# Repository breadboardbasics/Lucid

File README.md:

This is a repository for my Hackaday project here: http://hackaday.io/project/3715-tacs-lucid-dreaming-device

Thanks for checking out my project!
To make everything easier just click the download zip button on the right side of the main page of this repository. 
Then extract everthing to a folder. Next you should be able to view the board and schematic files with KiCad or
you can just view the schematic with the pdf that I included. 

All code that is used in this project will also be posted in this repository and will be updated as I progress through the 
project. 

Also for those wondering RevA (Revision A) is what I am calling the first version of the hardware. It is still a work in 
progress but is almost complete and ready for testing. 

**Disclaimer** - I am not responsible for any damages or injury related to this project
The project is very safe. It is battery powered and has a maximum of about 18v present on the board. Do not attempt to use 
the headset when it is connected to mains (the wall) in any way ex. you are powereing it with the programmer which is connected 
a desktop computer ect.

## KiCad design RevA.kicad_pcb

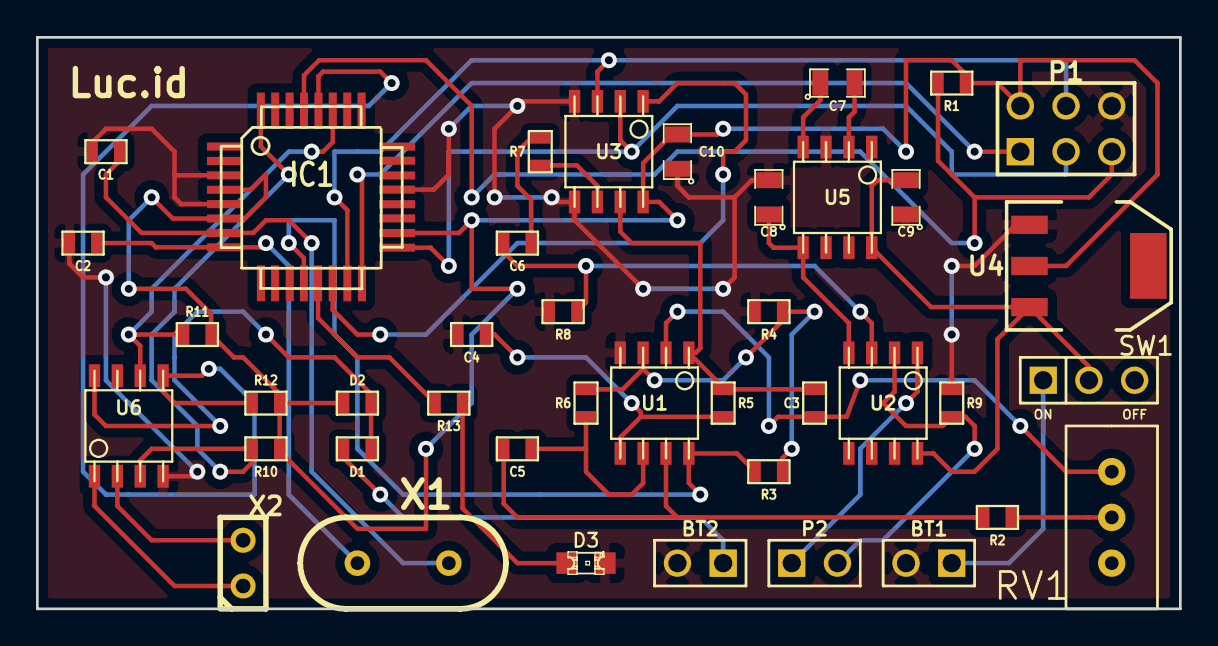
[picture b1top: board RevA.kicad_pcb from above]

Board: 2 copper layers, 63.5 x 31.8 mm, 41 parts (0 on the bottom side), 36 nets.

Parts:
BT1, BT2: BATTERY; PIN_ARRAY_2X1
C1, C2: 22pF; SM0603
C3, C4, C5, C6: .22uF; SM0603
C7, C8, C9, C10: 10uF; SM0805
D1, D2: DIODE; SM0603
D3: LED; LED-0805
IC1: ATMEGA328P-A; TQFP32
P1: ICSP; pin_array_3x2
P2: ELECTODES; PIN_ARRAY_2X1
R1, R2, R7, R10, R11, R12: 10k; SM0603
R3, R4: 2.2k; SM0603
R5, R6: 13k; SM0603
R8: 10M; SM0603
R9: 2.5k; SM0603
R13: 3.3k; SM0603
RV1: 20k; TRIMPOT_V
SW1: Power Switch; PIN_ARRAY_3X1
U1, U2: LM358; so-8
U3: MCP41010; so-8
U4: LM1117; SOT223
U5: ICL7660; so-8
U6: PCF8563; so-8
X1: 16MHz; HC-49V
X2: 32.768kHz; C1

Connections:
+5V: C10.2, D2.1, IC1.4, IC1.6, IC1.18, P1.2, R1.2, R10.2, R11.2, R12.2, U3.8, U4.2
+9V: C9.2, SW1.2, U2.8, U4.3, U5.8
-8V: C8.1, U2.4, U5.5
/INT: IC1.32, R10.1, U6.3
/MISO: IC1.16, P1.1
/MOSI: IC1.15, P1.4, U3.3
/OCON: IC1.12, R3.1, U1.8
/RST: IC1.29, P1.5, R1.1
/RTC_SCL: IC1.28, R12.1, U6.5
/RTC_SDA: IC1.27, R11.1, U6.6
/SCK: IC1.17, P1.3, U3.2
/led: IC1.13, R13.1
/potB: C3.2, R5.2, U1.1, U3.7
/potCS: IC1.14, U3.1
/potWiper: R7.1, U3.6
GND: BT1.2, BT2.2, C1.2, C2.2, C4.1, C8.2, C9.1, C10.1, D3.2, IC1.3, IC1.5, IC1.21, P1.6, R4.2, R8.1, R9.2, U1.4, U3.4, U3.5, U4.1, U5.3, U6.4
unnamed: C6.2, R8.2, U2.3
unnamed: C6.1, R7.2
unnamed: D1.2, D2.2, U6.8
unnamed: P2.2, R9.1, U2.2
unnamed: P2.1, U2.1
unnamed: U6.1, X2.1
unnamed: U6.2, X2.2
unnamed: D3.1, R13.2
unnamed: BT1.1, SW1.1
unnamed: C7.1, U5.4
unnamed: C7.2, U5.2
unnamed: C5.1, R2.2, U1.7
unnamed: R2.1, RV1.2
unnamed: R3.2, R4.1, R6.2, U1.3
unnamed: C2.1, IC1.8, X1.1
unnamed: C1.1, IC1.7, X1.2
unnamed: C3.1, RV1.3, U1.2
unnamed: C5.2, R6.1, U1.6
unnamed: C4.2, R5.1, U1.5
unnamed: BT2.1, D1.1

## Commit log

2014-12-30 Create Bill_Of_Materials
2014-12-30 Create RevA.sch
    This is the schematic file created in KiCad
2014-12-30 Board File
    Can only be opened in KiCad
2014-12-30 Updated Schems
2014-12-30 Library File For schematics
2014-12-30 Rename Lucid-cache.lib to RevA-cache.lib
2014-12-30 PDF of the schematics
2014-12-30 PDF of Schematics
2014-12-30 Read this
2015-01-03 Current code for the device
2015-03-24 Test folder
    A folder for test code and new things not yet ready
2015-03-24 Test line
2015-03-24 Change directory of bat
2015-03-24 compilation
2015-03-24 SPI now working
2015-03-25 Final code (not working yet)
2015-03-25 C code now working!
2015-03-25 Updated bat file
2015-03-25 New updated bat file
2015-03-25 All code working in rough state
2015-03-25 New icon shiny!
2015-03-25 compile
2015-03-25 Newer Icon shiny shiny!
